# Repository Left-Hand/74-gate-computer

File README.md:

# An-computer-which-is-made-up-of-74-logic-gates
An logic gate computer made of 74 gates
kechuang:https://www.kechuang.org/t/83193?
bilibili:https://space.bilibili.com/28690875/#/
QQ:924112068

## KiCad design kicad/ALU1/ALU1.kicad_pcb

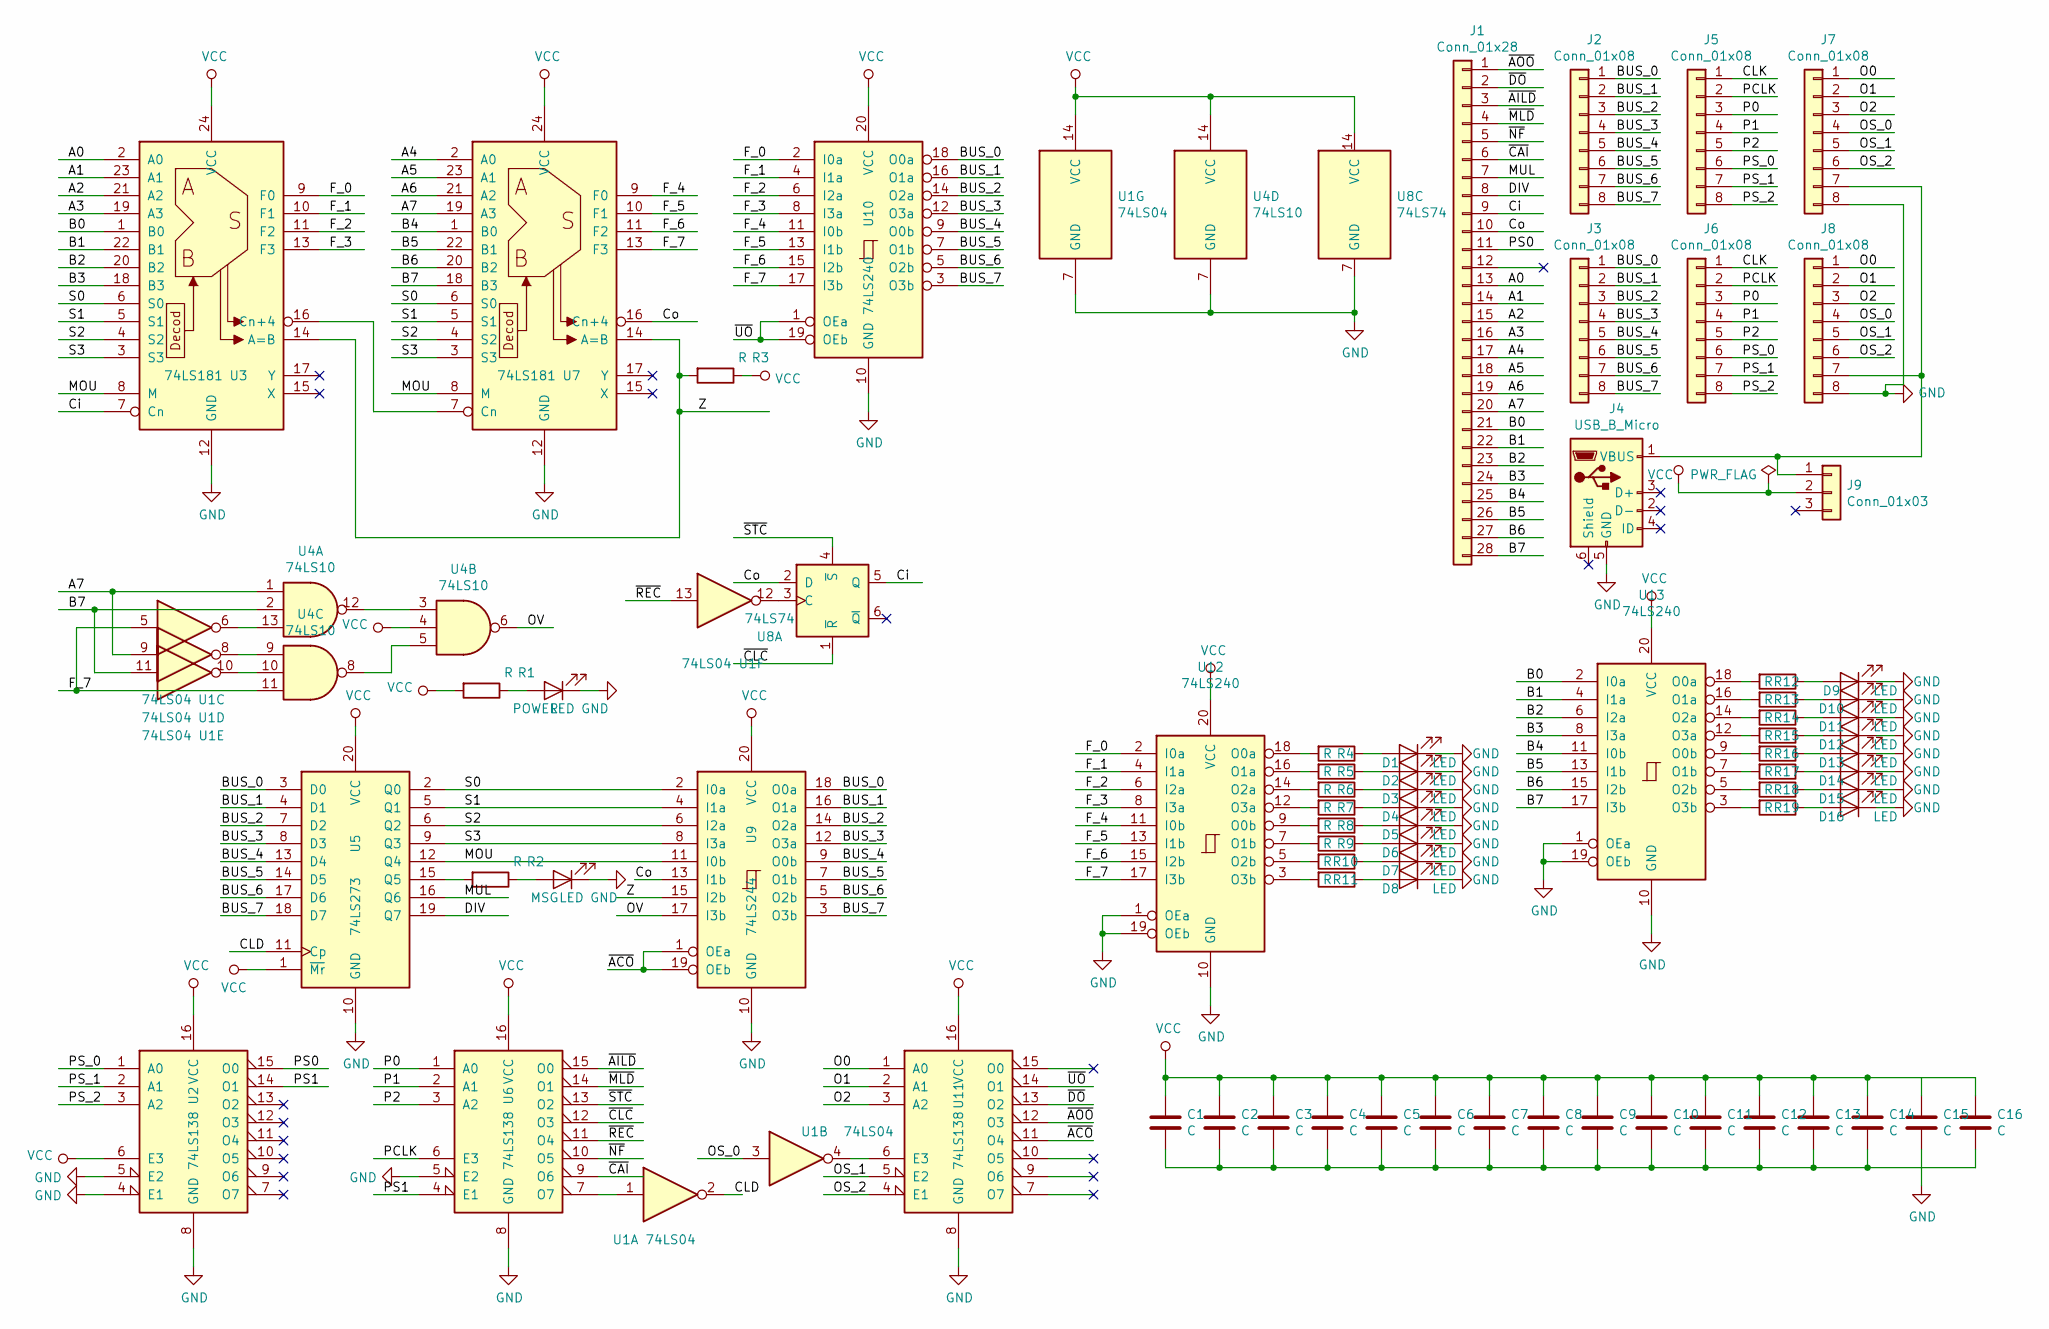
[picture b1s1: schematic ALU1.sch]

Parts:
C1, C2, C3, C4, C5, C6, C7, C8, C9, C10, C11, C12, C13, C14: C; C_Disc_D5.0mm_W2.5mm_P5.00mm
C15: C; CP_Radial_D5.0mm_P2.00mm
C16: C
D1, D2, D3, D4, D5, D6, D7, D8, D9, D10, D11, D12, D13, D14, D15, D16: LED; LED_Rectangular_W5.0mm_H2.0mm
J1: Conn_01x28; PinHeader_1x28_P2.54mm_Vertical
J2, J3, J5, J6, J7, J8: Conn_01x08; PinHeader_1x08_P2.54mm_Vertical
J4: USB_B_Micro; USB_Mini-B_Lumberg_2486_01_Horizontal
J9: Conn_01x03; PinHeader_1x03_P2.54mm_Vertical
MSG: LED; LED_Rectangular_W5.0mm_H2.0mm
POWER: LED; LED_Rectangular_W5.0mm_H2.0mm
R1, R2, R3, R4, R5, R6, R7, R8, R9, R10, R11, R12, R13, R14, R15, R16, R17, R18, R19: R; R_Axial_DIN0207_L6.3mm_D2.5mm_P10.16mm_Horizontal
U1: 74LS04; DIP-14_W7.62mm
U2, U6, U11: 74LS138; DIP-16_W7.62mm
U3, U7: 74LS181; DIP-24_W15.24mm
U4: 74LS10; DIP-14_W7.62mm
U5: 74LS273; DIP-20_W7.62mm
U8: 74LS74; DIP-14_W7.62mm
U9: 74LS244; DIP-20_W7.62mm
U10, U12, U13: 74LS240; DIP-20_W7.62mm

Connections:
/A0: J1.13, U3.2 (A0)
/A1: J1.14, U3.23 (A1)
/A2: J1.15, U3.21 (A2)
/A3: J1.16, U3.19 (A3)
/A4: J1.17, U7.2 (A0)
/A5: J1.18, U7.23 (A1)
/A6: J1.19, U7.21 (A2)
/A7: J1.20, U1.9, U4.1, U7.19 (A3)
/B0: J1.21, U3.1 (B0), U13.2 (I0a)
/B1: J1.22, U3.22 (B1), U13.4 (I1a)
/B2: J1.23, U3.20 (B2), U13.6 (I2a)
/B3: J1.24, U3.18 (B3), U13.8 (I3a)
/B4: J1.25, U7.1 (B0), U13.11 (I0b)
/B5: J1.26, U7.22 (B1), U13.13 (I1b)
/B6: J1.27, U7.20 (B2), U13.15 (I2b)
/B7: J1.28, U1.11, U4.2, U7.18 (B3), U13.17 (I3b)
/BUS_0: J2.1, J3.1, U5.3 (D0), U9.18 (O0a), U10.18 (O0a)
/BUS_1: J2.2, J3.2, U5.4 (D1), U9.16 (O1a), U10.16 (O1a)
/BUS_2: J2.3, J3.3, U5.7 (D2), U9.14 (O2a), U10.14 (O2a)
/BUS_3: J2.4, J3.4, U5.8 (D3), U9.12 (O3a), U10.12 (O3a)
/BUS_4: J2.5, J3.5, U5.13 (D4), U9.9 (O0b), U10.9 (O0b)
/BUS_5: J2.6, J3.6, U5.14 (D5), U9.7 (O1b), U10.7 (O1b)
/BUS_6: J2.7, J3.7, U5.17 (D6), U9.5 (O2b), U10.5 (O2b)
/BUS_7: J2.8, J3.8, U5.18 (D7), U9.3 (O3b), U10.3 (O3b)
/CLD: U1.2, U5.11 (Cp)
/CLK: J5.1, J6.1
/Ci: J1.9, U3.7 (Cn), U8.5 (Q)
/Co: J1.10, U7.16 (Cn+4), U8.2 (D), U9.13 (I1b)
/DIV: J1.8, U5.19 (Q7)
/F_0: U3.9 (F0), U10.2 (I0a), U12.2 (I0a)
/F_1: U3.10 (F1), U10.4 (I1a), U12.4 (I1a)
/F_2: U3.11 (F2), U10.6 (I2a), U12.6 (I2a)
/F_3: U3.13 (F3), U10.8 (I3a), U12.8 (I3a)
/F_4: U7.9 (F0), U10.11 (I0b), U12.11 (I0b)
/F_5: U7.10 (F1), U10.13 (I1b), U12.13 (I1b)
/F_6: U7.11 (F2), U10.15 (I2b), U12.15 (I2b)
/F_7: U1.5, U4.11, U7.13 (F3), U10.17 (I3b), U12.17 (I3b)
/MOU: U3.8 (M), U5.12 (Q4), U7.8 (M), U9.11 (I0b)
/MUL: J1.7, U5.16 (Q6)
/O0: J7.1, J8.1, U11.1 (A0)
/O1: J7.2, J8.2, U11.2 (A1)
/O2: J7.3, J8.3, U11.3 (A2)
/OS_0: J7.4, J8.4, U1.3
/OS_1: J7.5, J8.5, U11.5 (E2)
/OS_2: J7.6, J8.6, U11.4 (E1)
/OV: U4.6, U9.17 (I3b)
/P0: J5.3, J6.3, U6.1 (A0)
/P1: J5.4, J6.4, U6.2 (A1)
/P2: J5.5, J6.5, U6.3 (A2)
/PCLK: J5.2, J6.2, U6.6 (E3)
/PS0: J1.11, U2.15 (O0)
/PS1: U2.14 (O1), U6.4 (E1)
/PS_0: J5.6, J6.6, U2.1 (A0)
/PS_1: J5.7, J6.7, U2.2 (A1)
/PS_2: J5.8, J6.8, U2.3 (A2)
/S0: U3.6 (S0), U5.2 (Q0), U7.6 (S0), U9.2 (I0a)
/S1: U3.5 (S1), U5.5 (Q1), U7.5 (S1), U9.4 (I1a)
/S2: U3.4 (S2), U5.6 (Q2), U7.4 (S2), U9.6 (I2a)
/S3: U3.3 (S3), U5.9 (Q3), U7.3 (S3), U9.8 (I3a)
/Z: R3.2, U3.14 (A=B), U7.14 (A=B), U9.15 (I2b)
/~ACO: U9.1 (OEa), U9.19 (OEb), U11.11 (O4)
/~AILD: J1.3, U6.15 (O0)
/~AOO: J1.1, U11.12 (O3)
/~CAI: J1.6, U6.9 (O6)
/~CLC: U6.12 (O3), U8.1 (~R)
/~DO: J1.2, U11.13 (O2)
/~MLD: J1.4, U6.14 (O1)
/~NF: J1.5, U6.10 (O5)
/~REC: U1.13, U6.11 (O4)
/~STC: U6.13 (O2), U8.4 (~S)
/~UO: U10.1 (OEa), U10.19 (OEb), U11.14 (O1)
GND: C1.2, C2.2, C3.2, C4.2, C5.2, C6.2, C7.2, C8.2, C9.2, C10.2, C11.2, C12.2, C13.2, C14.2, C15.2, C16.2, D1.1 (K), D2.1 (K), D3.1 (K), D4.1 (K), D5.1 (K), D6.1 (K), D7.1 (K), D8.1 (K), D9.1 (K), D10.1 (K), D11.1 (K), D12.1 (K), D13.1 (K), D14.1 (K), D15.1 (K), D16.1 (K), J4.5 (GND), J7.8, J8.8, MSG.1 (K), POWER.1 (K), U1.7 (GND), U2.4 (E1), U2.5 (E2), U2.8 (GND), U3.12 (GND), U4.7 (GND), U5.10 (GND), U6.5 (E2), U6.8 (GND), U7.12 (GND), U8.7 (GND), U9.10 (GND), U10.10 (GND), U11.8 (GND), U12.1 (OEa), U12.10 (GND), U12.19 (OEb), U13.1 (OEa), U13.10 (GND), U13.19 (OEb)
unnamed: D1.2 (A), R4.1
unnamed: D2.2 (A), R5.1
unnamed: D3.2 (A), R6.1
unnamed: D4.2 (A), R7.1
unnamed: D5.2 (A), R8.1
unnamed: D6.2 (A), R9.1
unnamed: D7.2 (A), R10.1
unnamed: D8.2 (A), R11.1
unnamed: D9.2 (A), R12.1
unnamed: D10.2 (A), R13.1
unnamed: D11.2 (A), R14.1
unnamed: D12.2 (A), R15.1
unnamed: D13.2 (A), R16.1
unnamed: D14.2 (A), R17.1
unnamed: D15.2 (A), R18.1
unnamed: D16.2 (A), R19.1
unnamed: J4.1 (VBUS), J7.7, J8.7, J9.1
unnamed: MSG.2 (A), R2.1
unnamed: POWER.2 (A), R1.1
unnamed: R2.2, U5.15 (Q5)
unnamed: R4.2, U12.18 (O0a)
unnamed: R5.2, U12.16 (O1a)
unnamed: R6.2, U12.14 (O2a)
unnamed: R7.2, U12.12 (O3a)
unnamed: R8.2, U12.9 (O0b)
unnamed: R9.2, U12.7 (O1b)
unnamed: R10.2, U12.5 (O2b)
unnamed: R11.2, U12.3 (O3b)
unnamed: R12.2, U13.18 (O0a)
unnamed: R13.2, U13.16 (O1a)
unnamed: R14.2, U13.14 (O2a)
unnamed: R15.2, U13.12 (O3a)
unnamed: R16.2, U13.9 (O0b)
unnamed: R17.2, U13.7 (O1b)
unnamed: R18.2, U13.5 (O2b)
unnamed: R19.2, U13.3 (O3b)
unnamed: U1.1, U6.7 (O7)
unnamed: U1.4, U11.6 (E3)
unnamed: U1.6, U4.13
unnamed: U1.8, U4.9
unnamed: U1.10, U4.10
unnamed: U1.12, U8.3 (C)
unnamed: U3.16 (Cn+4), U7.7 (Cn)
unnamed: U4.5, U4.8
unnamed: U4.3, U4.12
VCC: C1.1, C2.1, C3.1, C4.1, C5.1, C6.1, C7.1, C8.1, C9.1, C10.1, C11.1, C12.1, C13.1, C14.1, C15.1, C16.1, J9.2, R1.2, R3.1, U1.14 (VCC), U2.6 (E3), U2.16 (VCC), U3.24 (VCC), U4.4, U4.14 (VCC), U5.1 (~Mr), U5.20 (VCC), U6.16 (VCC), U7.24 (VCC), U8.14 (VCC), U9.20 (VCC), U10.20 (VCC), U11.16 (VCC), U12.20 (VCC), U13.20 (VCC)

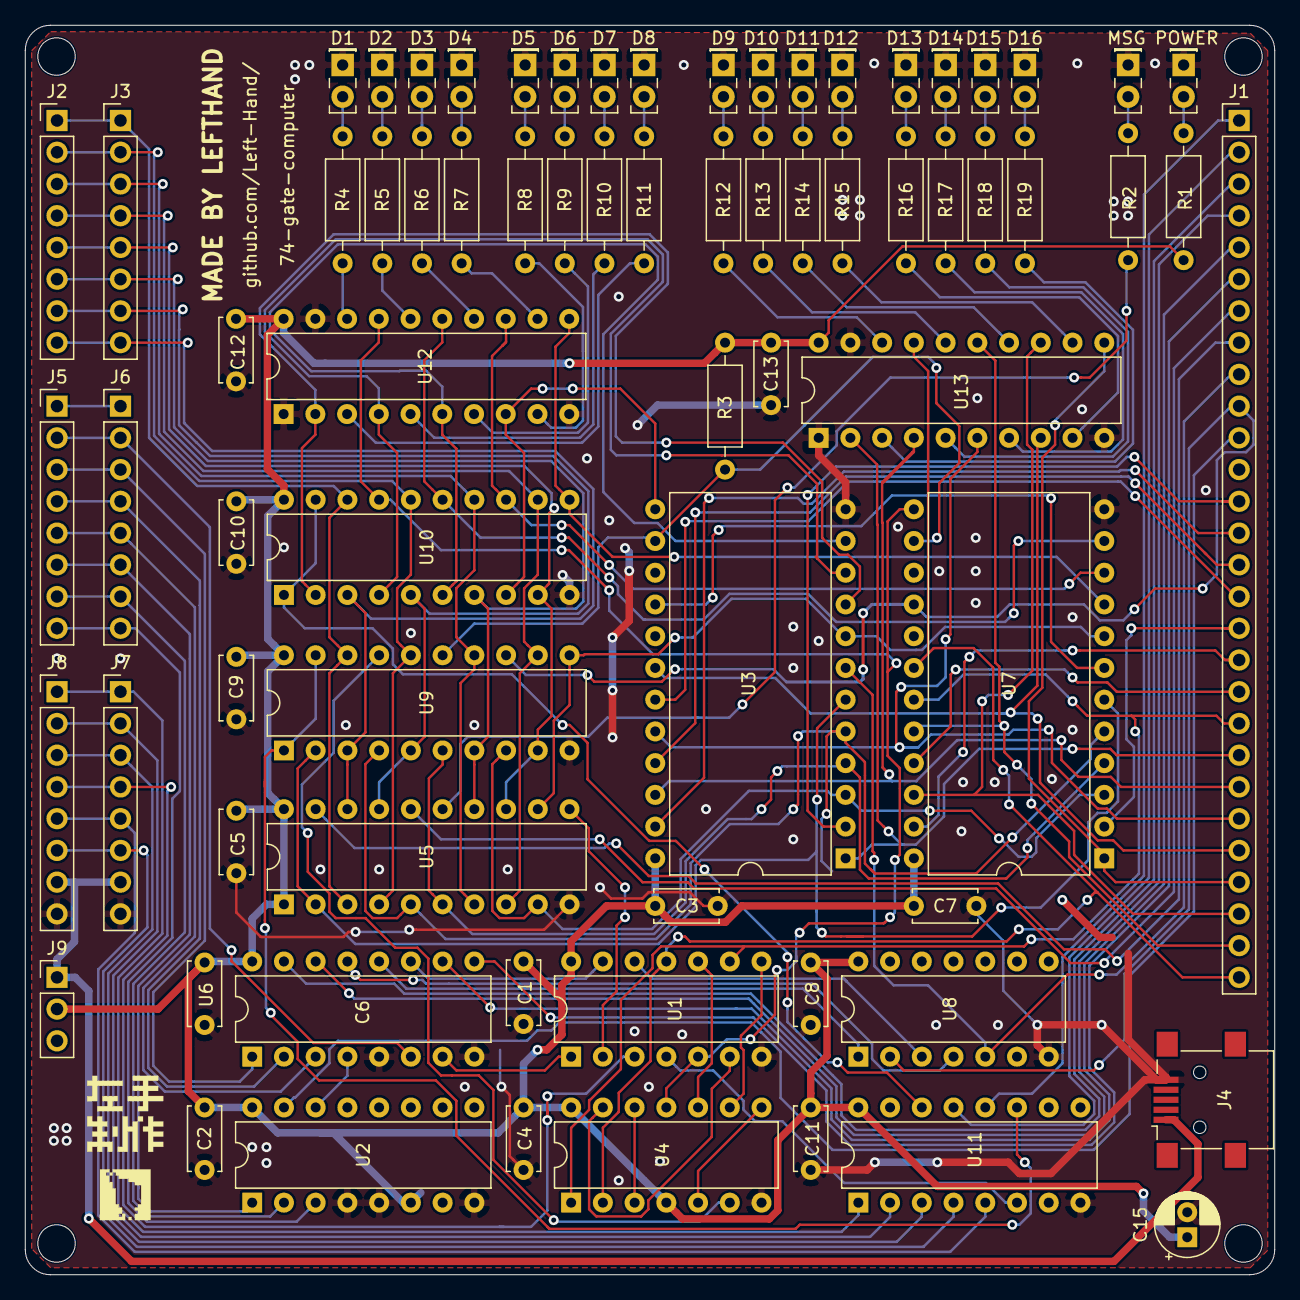
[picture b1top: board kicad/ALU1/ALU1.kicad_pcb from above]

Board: 2 copper layers, 100.0 x 100.0 mm, 73 parts (0 on the bottom side), 118 nets.

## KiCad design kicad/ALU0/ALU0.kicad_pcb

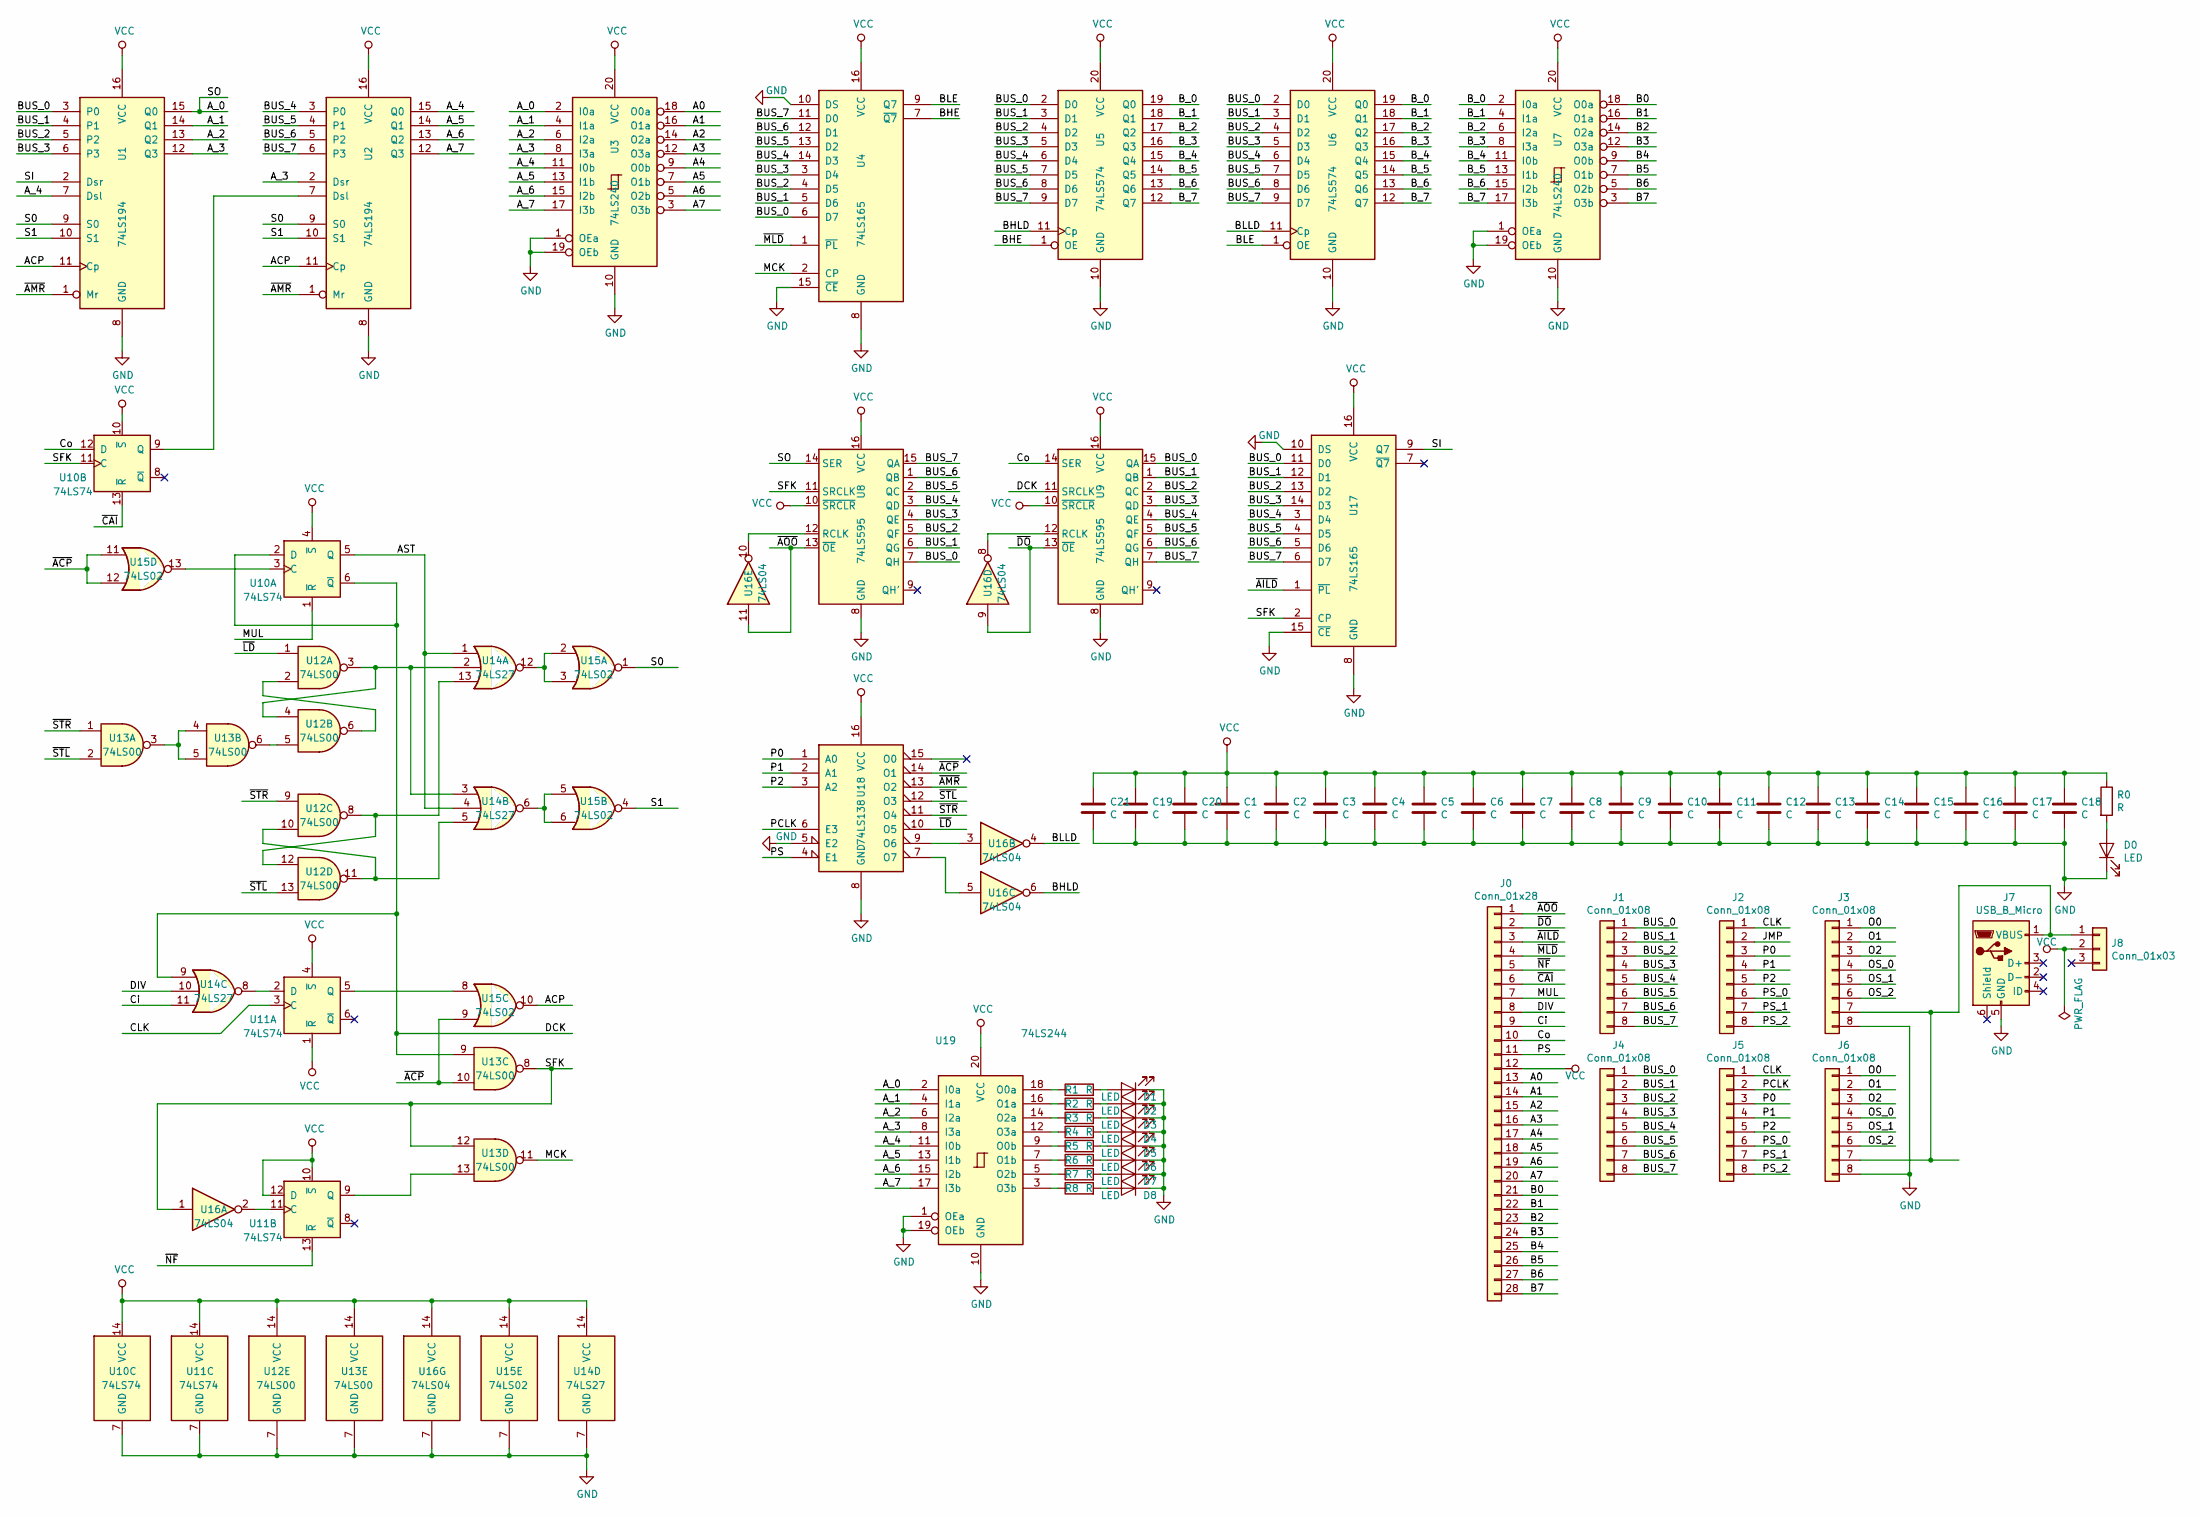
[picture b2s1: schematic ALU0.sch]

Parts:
C1, C2, C3, C4, C5, C6, C7, C8, C9, C10, C11, C12, C13, C14, C15, C16, C17, C18, C19, C20: C; C_Disc_D5.0mm_W2.5mm_P5.00mm
C21: C; CP_Radial_D5.0mm_P2.00mm
D0, D1, D2, D3, D4, D5, D6, D7, D8: LED; LED_Rectangular_W5.0mm_H2.0mm
J0: Conn_01x28; PinHeader_1x28_P2.54mm_Vertical
J1, J2, J3, J4, J5, J6: Conn_01x08; PinHeader_1x08_P2.54mm_Vertical
J7: USB_B_Micro; USB_Mini-B_Lumberg_2486_01_Horizontal
J8: Conn_01x03; PinHeader_1x03_P2.54mm_Vertical
R0, R1, R2, R3, R4, R5, R6, R7, R8: R; R_Axial_DIN0207_L6.3mm_D2.5mm_P10.16mm_Horizontal
U1, U2: 74LS194; DIP-16_W7.62mm
U3, U7: 74LS240; DIP-20_W7.62mm
U4, U17: 74LS165; DIP-16_W7.62mm
U5, U6: 74LS574; DIP-20_W7.62mm
U8, U9: 74LS595; DIP-16_W7.62mm
U10, U11: 74LS74; DIP-14_W7.62mm
U12, U13: 74LS00; DIP-14_W7.62mm
U14: 74LS27; DIP-14_W7.62mm
U15: 74LS02; DIP-14_W7.62mm
U16: 74LS04; DIP-14_W7.62mm
U18: 74LS138; DIP-16_W7.62mm
U19: 74LS244; DIP-20_W7.62mm

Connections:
/A0: J0.13, U3.18 (O0a)
/A1: J0.14, U3.16 (O1a)
/A2: J0.15, U3.14 (O2a)
/A3: J0.16, U3.12 (O3a)
/A4: J0.17, U3.9 (O0b)
/A5: J0.18, U3.7 (O1b)
/A6: J0.19, U3.5 (O2b)
/A7: J0.20, U3.3 (O3b)
/ACP: U1.11 (Cp), U2.11 (Cp), U15.10
/AST: U10.5 (Q), U14.1, U14.4
/A_0: U1.15 (Q0), U3.2 (I0a), U8.14 (SER), U19.2 (I0a)
/A_1: U1.14 (Q1), U3.4 (I1a), U19.4 (I1a)
/A_2: U1.13 (Q2), U3.6 (I2a), U19.6 (I2a)
/A_3: U1.12 (Q3), U2.2 (Dsr), U3.8 (I3a), U19.8 (I3a)
/A_4: U1.7 (Dsl), U2.15 (Q0), U3.11 (I0b), U19.11 (I0b)
/A_5: U2.14 (Q1), U3.13 (I1b), U19.13 (I1b)
/A_6: U2.13 (Q2), U3.15 (I2b), U19.15 (I2b)
/A_7: U2.12 (Q3), U3.17 (I3b), U19.17 (I3b)
/B0: J0.21, U7.18 (O0a)
/B1: J0.22, U7.16 (O1a)
/B2: J0.23, U7.14 (O2a)
/B3: J0.24, U7.12 (O3a)
/B4: J0.25, U7.9 (O0b)
/B5: J0.26, U7.7 (O1b)
/B6: J0.27, U7.5 (O2b)
/B7: J0.28, U7.3 (O3b)
/BHE: U4.7 (~Q7), U5.1 (OE)
/BHLD: U5.11 (Cp), U16.6
/BLE: U4.9 (Q7), U6.1 (OE)
/BLLD: U6.11 (Cp), U16.4
/BUS_0: J1.1, J4.1, U1.3 (P0), U4.6 (D7), U5.2 (D0), U6.2 (D0), U8.7 (QH), U9.15 (QA), U17.11 (D0)
/BUS_1: J1.2, J4.2, U1.4 (P1), U4.5 (D6), U5.3 (D1), U6.3 (D1), U8.6 (QG), U9.1 (QB), U17.12 (D1)
/BUS_2: J1.3, J4.3, U1.5 (P2), U4.4 (D5), U5.4 (D2), U6.4 (D2), U8.5 (QF), U9.2 (QC), U17.13 (D2)
/BUS_3: J1.4, J4.4, U1.6 (P3), U4.3 (D4), U5.5 (D3), U6.5 (D3), U8.4 (QE), U9.3 (QD), U17.14 (D3)
/BUS_4: J1.5, J4.5, U2.3 (P0), U4.14 (D3), U5.6 (D4), U6.6 (D4), U8.3 (QD), U9.4 (QE), U17.3 (D4)
/BUS_5: J1.6, J4.6, U2.4 (P1), U4.13 (D2), U5.7 (D5), U6.7 (D5), U8.2 (QC), U9.5 (QF), U17.4 (D5)
/BUS_6: J1.7, J4.7, U2.5 (P2), U4.12 (D1), U5.8 (D6), U6.8 (D6), U8.1 (QB), U9.6 (QG), U17.5 (D6)
/BUS_7: J1.8, J4.8, U2.6 (P3), U4.11 (D0), U5.9 (D7), U6.9 (D7), U8.15 (QA), U9.7 (QH), U17.6 (D7)
/B_0: U5.19 (Q0), U6.19 (Q0), U7.2 (I0a)
/B_1: U5.18 (Q1), U6.18 (Q1), U7.4 (I1a)
/B_2: U5.17 (Q2), U6.17 (Q2), U7.6 (I2a)
/B_3: U5.16 (Q3), U6.16 (Q3), U7.8 (I3a)
/B_4: U5.15 (Q4), U6.15 (Q4), U7.11 (I0b)
/B_5: U5.14 (Q5), U6.14 (Q5), U7.13 (I1b)
/B_6: U5.13 (Q6), U6.13 (Q6), U7.15 (I2b)
/B_7: U5.12 (Q7), U6.12 (Q7), U7.17 (I3b)
/CLK: J2.1, J5.1, U11.3 (C)
/Ci: J0.9, U14.11
/Co: J0.10, U9.14 (SER), U10.12 (D)
/DCK: U9.11 (SRCLK), U10.2 (D), U10.6 (~Q), U13.9, U14.9
/DIV: J0.8, U14.10
/MCK: U4.2 (CP), U13.11
/MUL: J0.7, U10.1 (~R)
/O0: J3.1, J6.1
/O1: J3.2, J6.2
/O2: J3.3, J6.3
/OS_0: J3.4, J6.4
/OS_1: J3.5, J6.5
/OS_2: J3.6, J6.6
/P0: J2.3, J5.3, U18.1 (A0)
/P1: J2.4, J5.4, U18.2 (A1)
/P2: J2.5, J5.5, U18.3 (A2)
/PS: J0.11, U18.4 (E1)
/PS_0: J2.6, J5.6
/PS_1: J2.7, J5.7
/PS_2: J2.8, J5.8
/S0: U1.9 (S0), U2.9 (S0), U15.1
/S1: U1.10 (S1), U2.10 (S1), U15.4
/SFK: U8.11 (SRCLK), U10.11 (C), U13.8, U13.12, U16.1, U17.2 (CP)
/SI: U1.2 (Dsr), U17.9 (Q7)
/~ACP: U13.10, U15.9, U15.11, U15.12, U18.14 (O1)
/~AILD: J0.3, U17.1 (~PL)
/~AMR: U1.1 (Mr), U2.1 (Mr), U18.13 (O2)
/~AOO: J0.1, U8.13 (~OE), U16.11
/~CAI: J0.6, U10.13 (~R)
/~DO: J0.2, U9.13 (~OE), U16.9
/~LD: U12.1, U18.10 (O5)
/~MLD: J0.4, U4.1 (~PL)
/~NF: J0.5, U11.13 (~R)
/~STL: U12.13, U13.2, U18.12 (O3)
/~STR: U12.9, U13.1, U18.11 (O4)
GND: C1.1, C2.1, C3.1, C4.1, C5.1, C6.1, C7.1, C8.1, C9.1, C10.1, C11.1, C12.1, C13.1, C14.1, C15.1, C16.1, C17.1, C18.1, C19.1, C20.1, C21.1, D0.1 (K), D1.1 (K), D2.1 (K), D3.1 (K), D4.1 (K), D5.1 (K), D6.1 (K), D7.1 (K), D8.1 (K), J3.8, J6.8, J7.5 (GND), U1.8 (GND), U2.8 (GND), U3.1 (OEa), U3.10 (GND), U3.19 (OEb), U4.8 (GND), U4.10 (DS), U4.15 (~CE), U5.10 (GND), U6.10 (GND), U7.1 (OEa), U7.10 (GND), U7.19 (OEb), U8.8 (GND), U9.8 (GND), U10.7 (GND), U11.7 (GND), U12.7 (GND), U13.7 (GND), U14.7 (GND), U15.7 (GND), U16.7 (GND), U17.8 (GND), U17.10 (DS), U17.15 (~CE), U18.5 (E2), U18.8 (GND), U19.1 (OEa), U19.10 (GND), U19.19 (OEb)
unnamed: D0.2 (A), R0.2
unnamed: D1.2 (A), R1.2
unnamed: D2.2 (A), R2.2
unnamed: D3.2 (A), R3.2
unnamed: D4.2 (A), R4.2
unnamed: D5.2 (A), R5.2
unnamed: D6.2 (A), R6.2
unnamed: D7.2 (A), R7.2
unnamed: D8.2 (A), R8.2
unnamed: J3.7, J6.7, J7.1 (VBUS), J8.1
unnamed: R1.1, U19.18 (O0a)
unnamed: R2.1, U19.16 (O1a)
unnamed: R3.1, U19.14 (O2a)
unnamed: R4.1, U19.12 (O3a)
unnamed: R5.1, U19.9 (O0b)
unnamed: R6.1, U19.7 (O1b)
unnamed: R7.1, U19.5 (O2b)
unnamed: R8.1, U19.3 (O3b)
unnamed: U10.3 (C), U15.13
unnamed: U2.7 (Dsl), U10.9 (Q)
unnamed: U11.2 (D), U14.8
unnamed: U11.5 (Q), U15.8
unnamed: U11.9 (Q), U13.13
unnamed: U11.11 (C), U16.2
unnamed: U12.2, U12.6
unnamed: U12.3, U12.4, U14.2, U14.3
unnamed: U12.5, U13.6
unnamed: U12.10, U12.11, U14.5
unnamed: U12.8, U12.12, U14.13
unnamed: U13.3, U13.4, U13.5
unnamed: U14.6, U15.5, U15.6
unnamed: U14.12, U15.2, U15.3
unnamed: U16.3, U18.9 (O6)
unnamed: U16.5, U18.7 (O7)
unnamed: U9.12 (RCLK), U16.8
unnamed: U8.12 (RCLK), U16.10
VCC: C1.2, C2.2, C3.2, C4.2, C5.2, C6.2, C7.2, C8.2, C9.2, C10.2, C11.2, C12.2, C13.2, C14.2, C15.2, C16.2, C17.2, C18.2, C19.2, C20.2, C21.2, J0.12, J8.2, R0.1, U1.16 (VCC), U2.16 (VCC), U3.20 (VCC), U4.16 (VCC), U5.20 (VCC), U6.20 (VCC), U7.20 (VCC), U8.10 (~SRCLR), U8.16 (VCC), U9.10 (~SRCLR), U9.16 (VCC), U10.4 (~S), U10.10 (~S), U10.14 (VCC), U11.1 (~R), U11.4 (~S), U11.10 (~S), U11.12 (D), U11.14 (VCC), U12.14 (VCC), U13.14 (VCC), U14.14 (VCC), U15.14 (VCC), U16.14 (VCC), U17.16 (VCC), U18.16 (VCC), U19.20 (VCC)

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
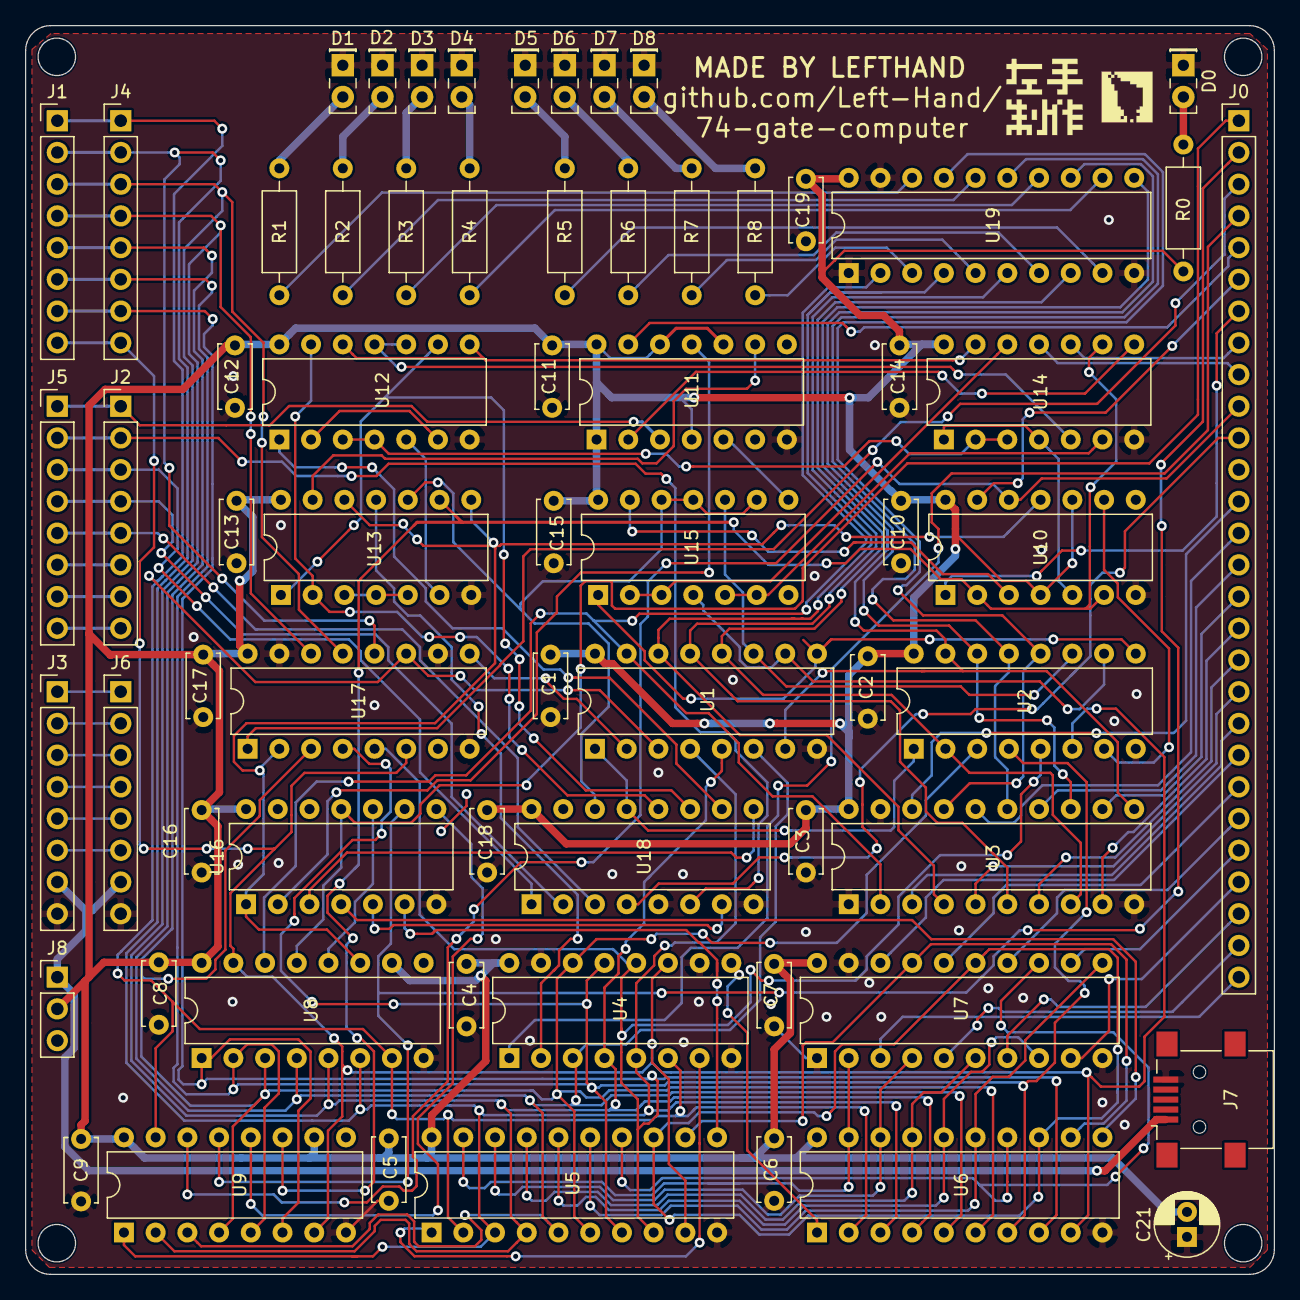
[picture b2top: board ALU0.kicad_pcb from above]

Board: 2 copper layers, 100.0 x 100.0 mm, 66 parts (0 on the bottom side), 120 nets.
